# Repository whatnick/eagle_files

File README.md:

Eagle Files
===========

Eagle Files for various projects. These include:

1: Xadow SD Card Module

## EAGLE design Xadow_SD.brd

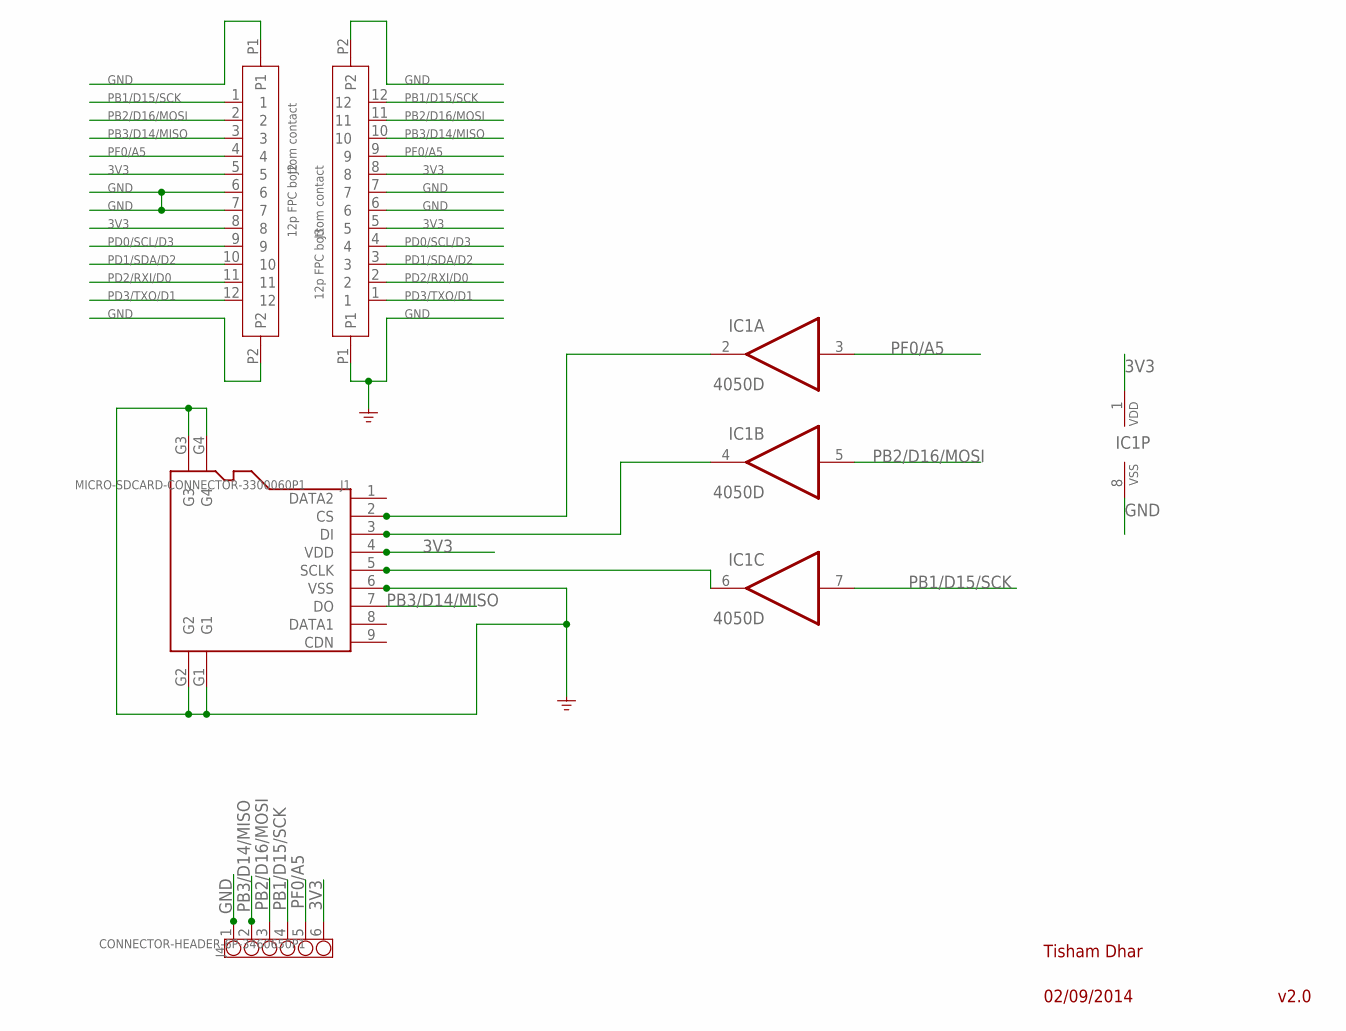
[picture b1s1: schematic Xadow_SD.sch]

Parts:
IC1: 4050D; SO16
J1: MICRO-SDCARD-CONNECTOR-3300060P1; 9P-SMD-W-RING
J2, J3: 12p FPC bottom contact; 12P-0.5
J4: CONNECTOR-HEADER-6P-3460650P1; 1X6P-2.54-2.54-11.6-3.0-BLACK-MALE

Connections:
3V3: IC1.1 (VDD), J1.4 (VDD), J2.5, J2.8, J3.5, J3.8, J4.6
CS: IC1.2 (O), J1.2 (CS)
GND: IC1.8 (VSS), J1.6 (VSS), J1.G1, J1.G2, J1.G3, J1.G4, J2.6, J2.7, J2.P1, J2.P2, J3.6, J3.7, J3.P1, J3.P2, J4.1
MOSI: IC1.4 (O), J1.3 (DI)
PB1/D15/SCK: IC1.7 (I), J2.1, J3.12, J4.4
PB2/D16/MOSI: IC1.5 (I), J2.2, J3.11, J4.3
PB3/D14/MISO: J1.7 (DO), J2.3, J3.10, J4.2
PD0/SCL/D3: J2.9, J3.4
PD1/SDA/D2: J2.10, J3.3
PD2/RXI/D0: J2.11, J3.2
PD3/TXO/D1: J2.12, J3.1
PF0/A5: IC1.3 (I), J2.4, J3.9, J4.5
SCK: IC1.6 (O), J1.5 (SCLK)

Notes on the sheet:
Tisham Dhar
02/09/2014
v2.0

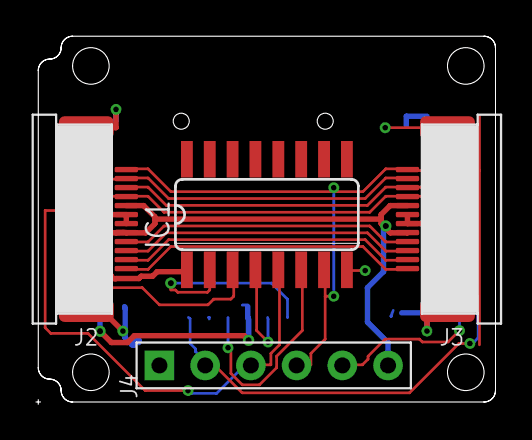
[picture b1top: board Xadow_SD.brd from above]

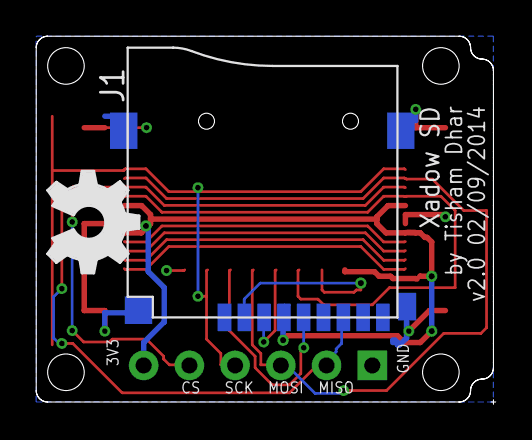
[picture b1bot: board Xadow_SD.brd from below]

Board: 2 copper layers, 25.4 x 20.3 mm, 6 parts (2 on the bottom side), 13 nets.

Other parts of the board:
U$3: OSHW_FILLX200_NOTEXT

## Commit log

2014-08-27 Add 6-pin header
2014-09-02 Add labels and move graphics
2014-09-02 Clean up labels
2015-03-11 Neaten up routing
2015-03-18 Flip SD holder
2015-03-18 Change VCC wire width
